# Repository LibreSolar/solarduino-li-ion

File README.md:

# Solarduino Li-Ion
Solar charge controller with integrated 12 V Li-Ion BMS

**Remark:** This charge controller is not maintained anymore and firmware + hardware might contain serious bugs. Use at your own risk!

Features so far: 

- 12 V LiFePO4 BMS (4 cells)
- 8A MPPT charger
- 50V max PV input
- 16V max. DCDC output = battery voltage
- Arduino-compatible (ATmega 328P used)
- Expandable via break-out of unused ports to standard 2.54 pin-pitch headers (e.g. used for display, communication like CAN/RS485, etc.)

Built-in protection:
- Overvoltage
- Undervoltage
- Overcurrent
- Overtemperature (via software)
- PV short circuit
- PV reverse polarity (via diode)
- Battery reverse polarity (destructive, fuse is blown)

# Firmware
The last version of the firmware based on Arduino can be found in the firmware directory.

# Known issues
- The current measurement using the INA168 does not work properly. The output should not be directly connected to the ADC, but should be buffed using an Op-amp in between.

# Roadmap
- My plan for the future is to separate the BMS system and the charge controller. Separate modules make the system more flexible. For a new, extended version of the BMS system see my other project here on github.
- A new version of the Solarduino charge controller will be capable of 12-24V and 12 A, thus just perfect for one large 60-cell PV panel in a 24V system.

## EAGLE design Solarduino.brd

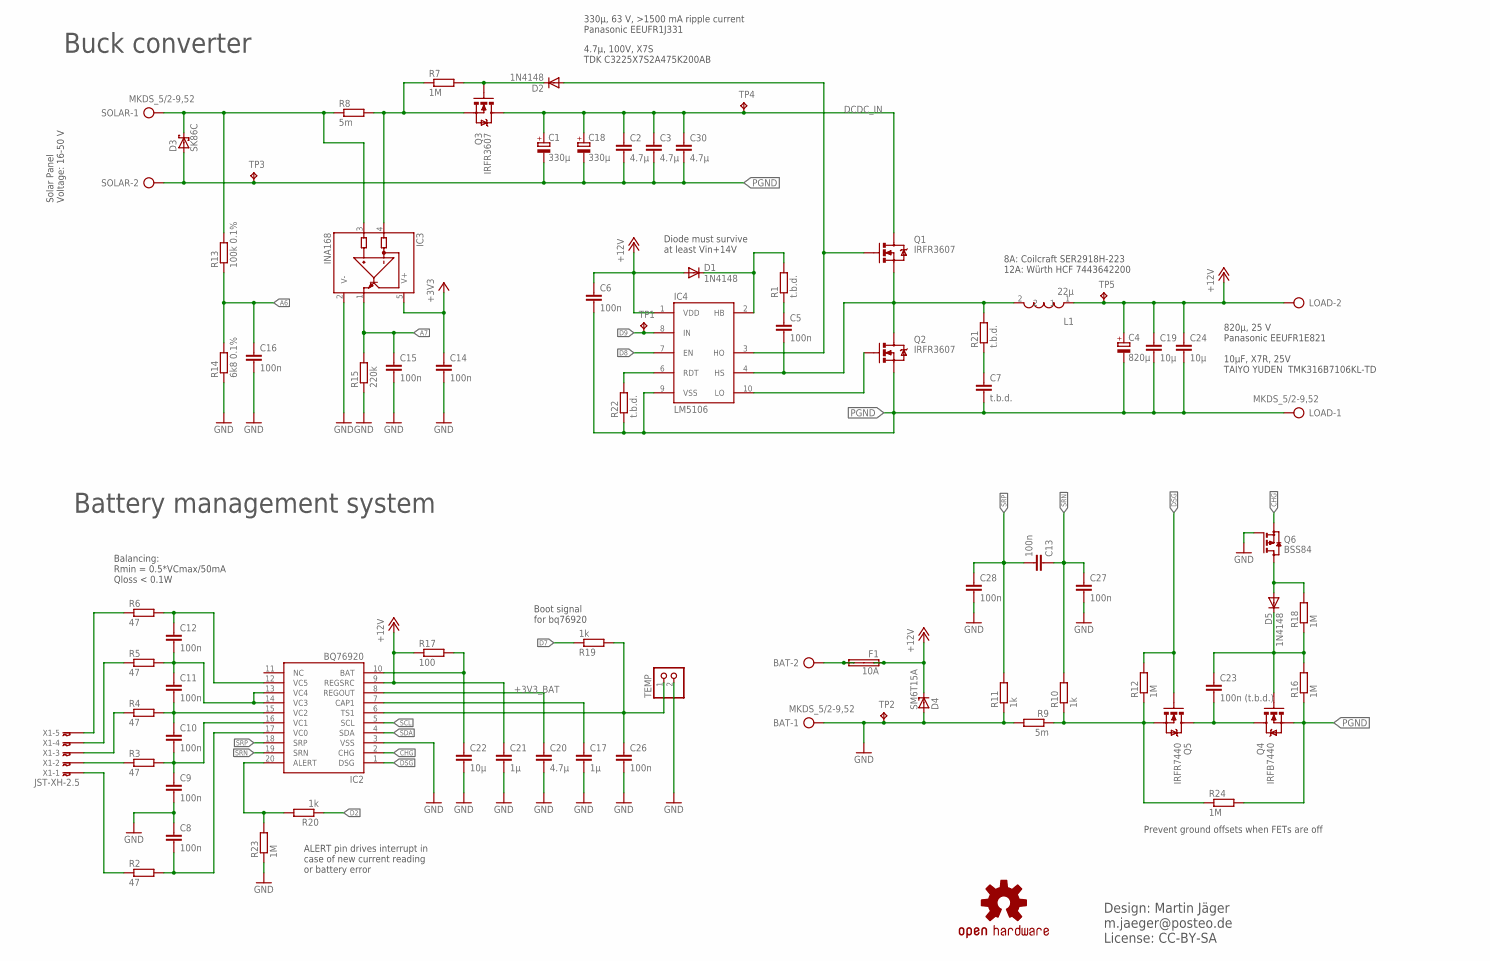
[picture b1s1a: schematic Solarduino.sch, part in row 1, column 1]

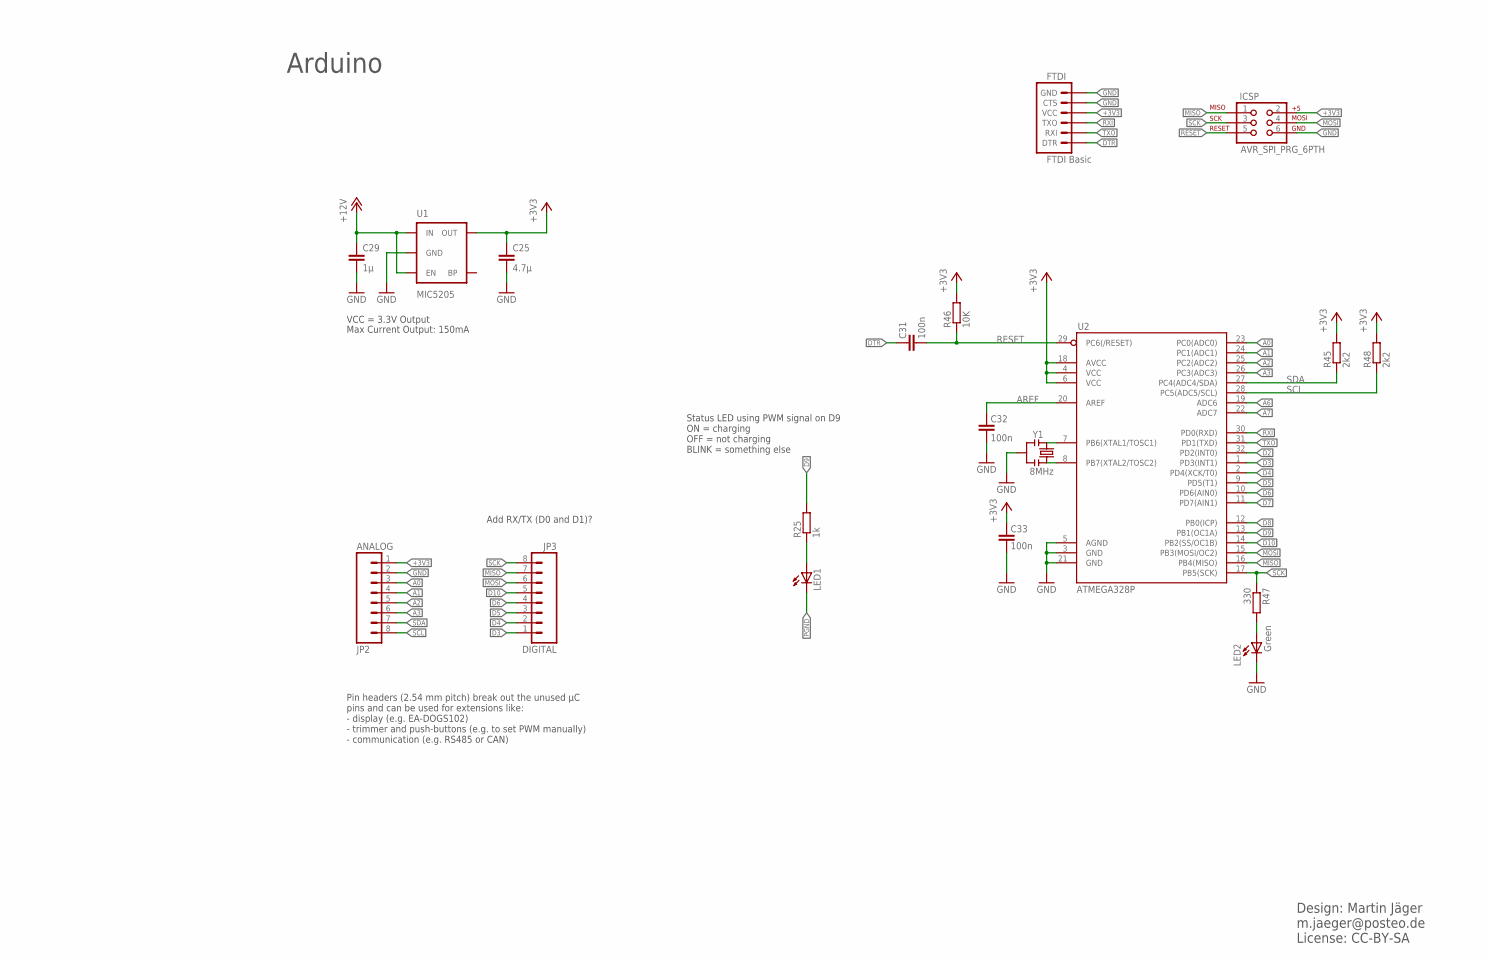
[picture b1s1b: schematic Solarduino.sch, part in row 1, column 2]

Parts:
BAT: MKDS_5/2-9,52; MKDS_5/2-952
C1, C18: 330µ; E5-13; MPN EEUFR1J331B
C2, C3, C30: 4.7µ; C1210; MPN C3225X7S2A475K200AB
C4: 820µ; E5-10,5; MPN EEUFR1E821B
C5, C6, C8, C9, C10, C11, C12, C13, C14, C15, C16, C26, C27, C28, C31, C32: 100n; C0805; MPN 08055C104KAT2A
C7: t.b.d.; C0805; MPN 08055C104KAT2A
C17, C21, C29: 1µ; C0805; MPN 08053C105KAT2A
C19, C22, C24: 10µ; C1206; MPN TMK316B7106KL-TD
C20, C25: 4.7µ; C0805; MPN 0805YC475KAT2A
C23: 100n (t.b.d.); C0805; MPN 08055C104KAT2A
C33: 100n; C0805; MPN 08055C104JAT2A
D1, D2, D5: 1N4148; SOD323-R; MPN 1N4148WS-E3-08
D3: SK86C; SMC; MPN SK56C
D4: SM6T15A; SMB; MPN P6SMBJ15A
F1: 10A; SHK20Q
FTDI: FTDI Basic; 1X06; MPN 2212S-06SG-85
IC2: BQ76920; TSSOP20
IC3: INA168; SOT23-5; MPN INA168NA/250.
IC4: LM5106; VSSOP10; MPN LM5106MM/NOPB
ICSP: AVR_SPI_PRG_6PTH; 2X3
JP2: ANALOG; 1X08_ROUND
JP3: DIGITAL; 1X08_ROUND
L1: 22µ; WE-HCF_2818_7443643300; MPN SER2918H-223KL
LED1: LED3MM; MPN MCL034GD
LED2: Green; 0603-LED-ALT1; MPN MCL034GD
LOAD: MKDS_5/2-9,52; MKDS_5/2-952
N1: OSHW-LOGOM; OSHW-LOGO-M
Q1, Q2, Q3: IRFR3607; DPAK; MPN IRFR3607PBF
Q4: IRFB7440; DPAK; MPN IRFR7440TRPBF
Q5: IRFR7440; DPAK; MPN IRFR7440TRPBF
Q6: BSS84; SOT23; MPN BSS84-7-F
R1, R22: t.b.d.; R0805; MPN CR0805-FX-1001ELF
R2, R3, R4, R5, R6: 47; R2512; MPN MCHP122WF470JT4E
R7, R12, R16, R18, R23, R24: 1M; R0805; MPN CR0805-FX-1004ELF.
R8, R9: 5m; R2512; MPN CRF2512-FX-R005ELF
R10, R11, R19, R20, R25: 1k; R0805; MPN CR0805-FX-1001ELF
R13: 100k 0.1%; R0805; MPN ERA6AEB104V
R14: 6k8 0.1%; R0805; MPN ERA6AEB682V
R15: 220k; R0805; MPN CHV0805-FX-2203ELF
R17: 100; R0805; MPN CR0805-FX-1000-ELF
R21: t.b.d.; R2010; MPN CRM2010-JW-2R2ELF
R45, R48: 2k2; R0805; MPN CR0805-FX-1001ELF
R46: 10K; R0805; MPN CR0805-FX-1002ELF
R47: 330; R0805; MPN CR0805-FX-3300ELF
SOLAR: MKDS_5/2-9,52; MKDS_5/2-952
TEMP: PINHD-1X2/90; 1X02/90; MPN MC34745
TP1, TP2, TP3, TP4, TP5: TPPAD1-13; P1-13
U1: MIC5205; SOT23-5; MPN MIC5205-3.3YM5 TR
U2: ATMEGA328P; TQFP32-08; MPN ATMEGA328P-AU
X1: JST-XH-2.5; S5B-XH; MPN S5B-XH-A (LF)(SN)
Y1: 8MHz; RESONATOR-SMD; MPN CSTCE8M00G55-R0

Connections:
+3V3: C14.1, C25.1, C33.2, FTDI.4 (VCC), IC3.5 (V+), ICSP.2, JP2.1, R45.2, R46.2, R48.2, U1.5 (OUT), U2.4 (VCC), U2.6 (VCC), U2.18 (AVCC)
+3V3_BAT: C20.1, IC2.8 (REGOUT)
+12V: C4.+, C6.1, C19.1, C21.1, C24.1, C29.1, D1.A, D4.C, F1.1A, F1.1B, IC2.9 (REGSRC), IC4.1 (VDD), L1.1, LOAD.2, R17.1, TP5.TP, U1.1 (IN), U1.3 (EN)
A0: JP2.3, U2.23 (PC0(ADC0))
A1: JP2.4, U2.24 (PC1(ADC1))
A2: JP2.5, U2.25 (PC2(ADC2))
A3: JP2.6, U2.26 (PC3(ADC3))
A6: C16.1, R13.1, R14.2, U2.19 (ADC6)
A7: C15.1, IC3.1 (OUT), R15.2, U2.22 (ADC7)
ALERT: IC2.20 (ALERT), R20.2, R23.2
AREF: C32.2, U2.20 (AREF)
BAT+: BAT.2, F1.2A, F1.2B
CHG: IC2.2 (CHG), Q6.2 (S)
D2: R20.1, U2.32 (PD2(INT0))
D3: JP3.1, U2.1 (PD3(INT1))
D4: JP3.2, U2.2 (PD4(XCK/T0))
D5: JP3.3, U2.9 (PD5(T1))
D6: JP3.4, U2.10 (PD6(AIN0))
D7: R19.1, U2.11 (PD7(AIN1))
D8: IC4.7 (EN), U2.12 (PB0(ICP))
D9: IC4.8 (IN), R25.2, TP1.TP, U2.13 (PB1(OC1A))
D10: JP3.5, U2.14 (PB2(SS/OC1B))
DCDC_IN: C1.+, C2.1, C3.1, C18.+, C30.1, Q1.4 (D), Q3.4 (D), TP4.TP
DSG: IC2.1 (DSG), Q5.1 (G), R12.2
DTR: C31.2, FTDI.1 (DTR)
D_LS: C5.2, IC4.4 (HS), L1.2, Q1.3 (S), Q2.4 (D), R21.2
GND: BAT.1, C8.1, C9.2, C14.2, C15.2, C16.2, C17.2, C20.2, C21.2, C22.2, C25.2, C26.2, C27.2, C28.2, C29.2, C32.1, C33.1, D4.A, FTDI.5 (CTS), FTDI.6 (GND), IC2.3 (VSS), IC3.2 (V-), ICSP.6, JP2.2, LED2.C, Q6.1 (G), R9.2, R11.1, R14.1, R15.1, R23.1, TEMP.2, TP2.TP, U1.2 (GND), U2.3 (GND), U2.5 (AGND), U2.21 (GND), Y1.2
MISO: ICSP.1, JP3.7, U2.16 (PB4(MISO))
MOSI: ICSP.4, JP3.6, U2.15 (PB3(MOSI/OC2))
unnamed: IC3.4 (IN-), Q3.3 (S), R7.1, R8.2
unnamed: IC4.10 (LO), Q2.1 (G)
unnamed: LED2.A, R47.2
unnamed: D2.A, IC4.3 (HO), Q1.1 (G)
unnamed: D1.C, IC4.2 (HB), R1.2
unnamed: C23.1, D5.C, Q4.1 (G), R16.2, R18.1
unnamed: R3.1, X1.P$2
unnamed: C5.1, R1.1
unnamed: C22.1, IC2.10 (BAT), R17.2
unnamed: C10.1, C11.2, IC2.15 (VC2), R4.2
unnamed: C11.1, C12.2, IC2.13 (VC4), IC2.14 (VC3), R5.2
unnamed: R2.1, X1.P$1
unnamed: C12.1, IC2.12 (VC5), R6.2
unnamed: C8.2, IC2.17 (VC0), R2.2
unnamed: R4.1, X1.P$3
unnamed: C9.1, C10.2, IC2.16 (VC1), R3.2
unnamed: R5.1, X1.P$4
unnamed: D5.A, Q6.3 (D), R18.2
unnamed: D2.C, Q3.1 (G), R7.2
unnamed: U2.8 (PB7(XTAL2/TOSC2)), Y1.3
unnamed: U2.7 (PB6(XTAL1/TOSC1)), Y1.1
unnamed: Q5.3 (S), R9.1, R10.1, R12.1, R24.1
unnamed: C23.2, Q4.4 (D), Q5.4 (D)
unnamed: IC4.6 (RDT), R22.2
unnamed: R6.1, X1.P$5
unnamed: C17.1, IC2.7 (CAP1)
unnamed: C7.1, R21.1
unnamed: LED1.A, R25.1
NTC: C26.1, IC2.6 (TS1), R19.2, TEMP.1
PGND: C1.-, C2.2, C3.2, C4.-, C6.2, C7.2, C18.-, C19.2, C24.2, C30.2, D3.A, IC4.9 (VSS), LED1.K (C), LOAD.1, Q2.3 (S), Q4.3 (S), R16.1, R22.1, R24.2, SOLAR.2, TP3.TP
RESET: C31.1, ICSP.5, R46.1, U2.29 (PC6(/RESET))
RXI: FTDI.3 (TXO), U2.30 (PD0(RXD))
SCK: ICSP.3, JP3.8, R47.1, U2.17 (PB5(SCK))
SCL: IC2.5 (SCL), JP2.8, R48.1, U2.28 (PC5(ADC5/SCL))
SDA: IC2.4 (SDA), JP2.7, R45.1, U2.27 (PC4(ADC4/SDA))
SOLAR+: D3.C, IC3.3 (IN+), R8.1, R13.2, SOLAR.1
SRN: C13.1, C27.1, IC2.19 (SRN), R10.2
SRP: C13.2, C28.1, IC2.18 (SRP), R11.2
TXO: FTDI.2 (RXI), U2.31 (PD1(TXD))

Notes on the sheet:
330µ, 63 V, >1500 mA ripple current Panasonic EEUFR1J331
820µ, 25 V Panasonic EEUFR1E821 10µF, X7R, 25V TAIYO YUDEN TMK316B7106KL-TD
Balancing: Rmin = 0.5*VCmax/50mA Qloss < 0.1W
Solar Panel Voltage: 16-50 V
Diode must survive at least Vin+14V
Arduino
Add RX/TX (D0 and D1)?
Boot signal for bq76920
ALERT pin drives interrupt in case of new current reading or battery error
Max Current Output: 150mA
VCC = 3.3V Output
Pin headers (2.54 mm pitch) break out the unused µC pins and can be used for extensions like: - display (e.g. EA-DOGS102) - trimmer and push-buttons (e.g. to set PWM manually) - communication (e.g. RS485 or CAN)
Design: Martin Jäger m.jaeger@posteo.de License: CC-BY-SA
Buck converter
Battery management system
Prevent ground offsets when FETs are off
4.7µ, 100V, X7S TDK C3225X7S2A475K200AB
Status LED using PWM signal on D9 ON = charging OFF = not charging BLINK = something else
8A: Coilcraft SER2918H-223 12A: Würth HCF 7443642200

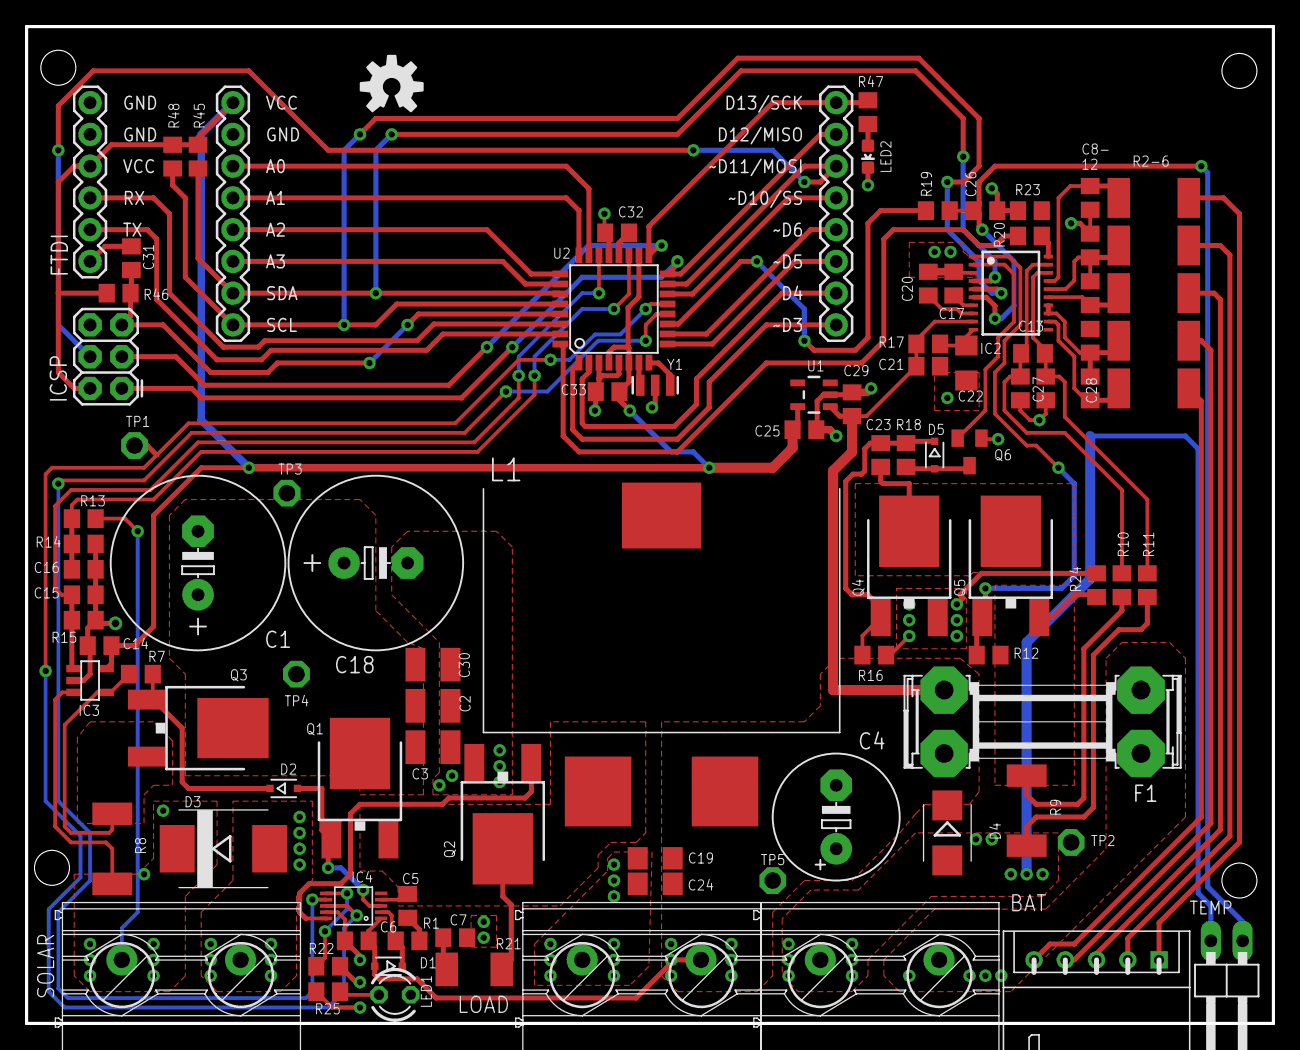
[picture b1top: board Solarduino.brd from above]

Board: 2 copper layers, 99.7 x 79.7 mm, 98 parts (0 on the bottom side), 68 nets.

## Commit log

2016-04-25 Upload of board files V0.3
2016-04-25 Added picture of soldered board
2019-03-19 Firmware added (latest version from several years ago)

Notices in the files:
parts and their libraries:
SparkFun-Connectors: Licensing: Creative Commons ShareAlike 4.0 International - https://creativecommons.org/licenses/by-sa/4.0
PowerMagnetics: Copyright: Würth Elektronik
